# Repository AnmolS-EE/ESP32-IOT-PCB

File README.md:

# ESP32-IOT-PCB
IN Progress...Stay Tuned

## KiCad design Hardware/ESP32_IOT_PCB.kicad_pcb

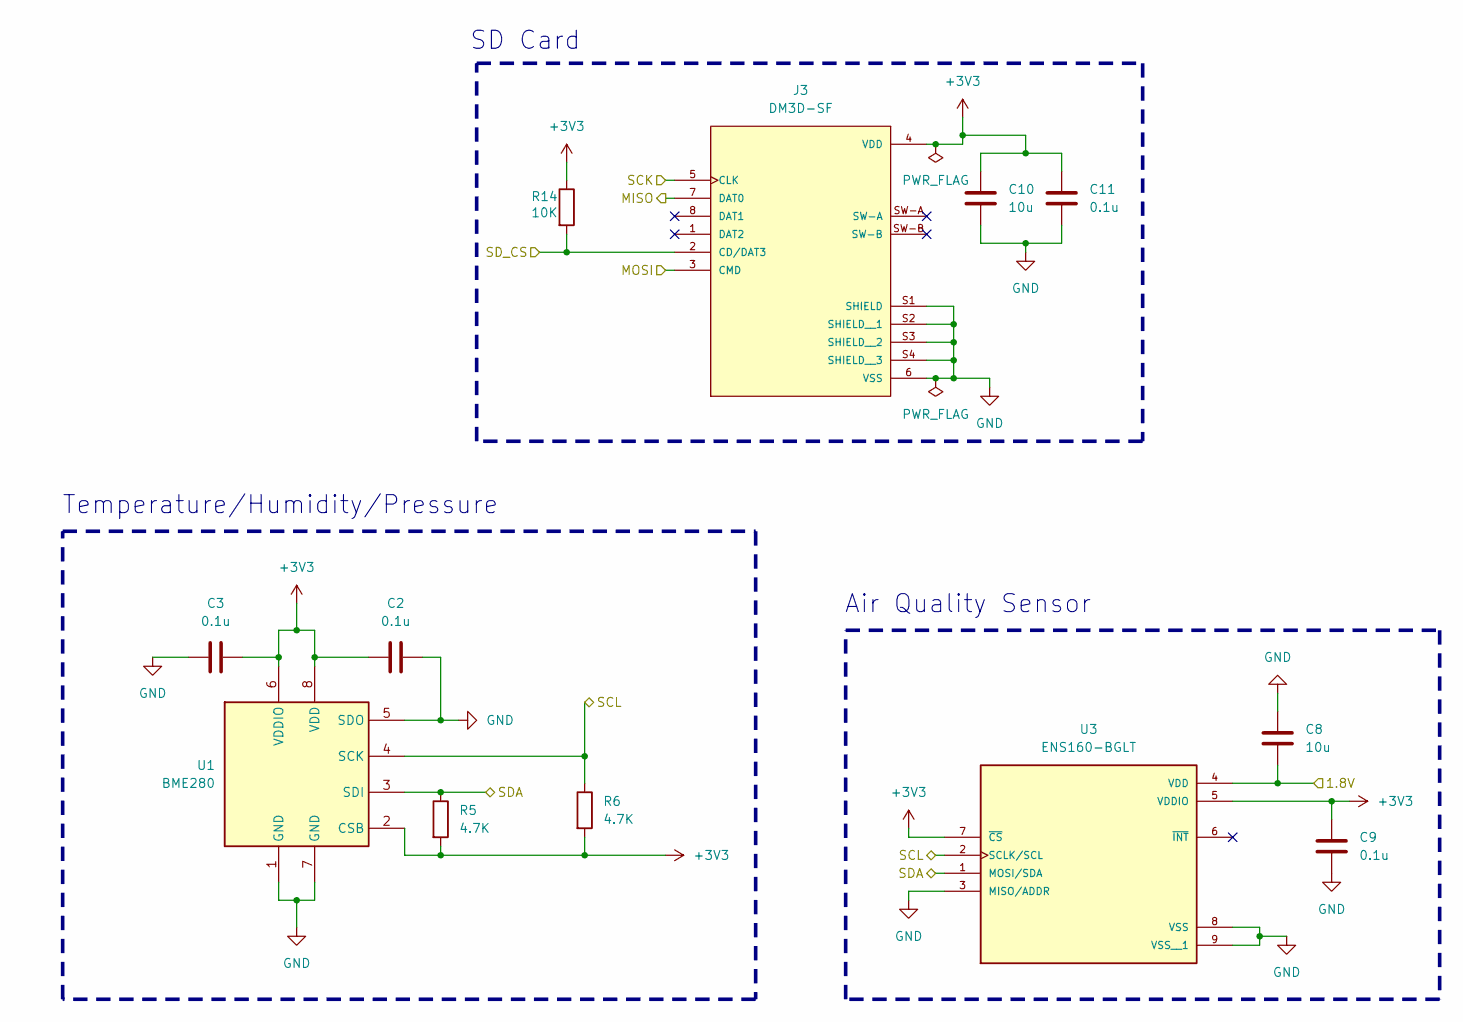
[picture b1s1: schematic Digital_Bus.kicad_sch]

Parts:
C2, C3, C9, C11: 0.1u; C_0805_2012Metric
C8, C10: 10u; C_0805_2012Metric
J3: DM3D-SF; HRS_DM3D-SF; PARTREV 2017.1
R5, R6: 4.7K; R_0805_2012Metric
R14: 10K; R_0805_2012Metric
U1: BME280; Bosch_LGA-8_2.5x2.5mm_P0.65mm_ClockwisePinNumbering
U3: ENS160-BGLT; XDCR_ENS160-BGLT; PARTREV 1.3

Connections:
+3V3: C2.1, C3.1, C9.1, C10.1, C11.1, J3.4 (VDD), R5.2, R6.2, R14.1, U1.2 (CSB), U1.6 (VDDIO), U1.8 (VDD), U3.5 (VDDIO), U3.7 (~CS); also elsewhere on the board
/Digital Bus/1.8V: C8.2, U3.4 (VDD); also elsewhere on the board
/Digital Bus/MISO: J3.7 (DAT0); also elsewhere on the board
/Digital Bus/MOSI: J3.3 (CMD); also elsewhere on the board
/Digital Bus/SCK: J3.5 (CLK); also elsewhere on the board
/Digital Bus/SCL: R6.1, U1.4 (SCK), U3.2 (SCLK/SCL); also elsewhere on the board
/Digital Bus/SDA: R5.1, U1.3 (SDI), U3.1 (MOSI/SDA); also elsewhere on the board
/Digital Bus/SD_CS: J3.2 (CD/DAT3), R14.2; also elsewhere on the board
GND: C2.2, C3.2, C8.1, C9.2, C10.2, C11.2, J3.6 (VSS), J3.S1 (SHIELD), J3.S2 (SHIELD__1), J3.S3 (SHIELD__2), J3.S4 (SHIELD__3), U1.1 (GND), U1.5 (SDO), U1.7 (GND), U3.3 (MISO/ADDR), U3.8 (VSS), U3.9 (VSS__1); also elsewhere on the board

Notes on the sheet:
SD Card
Temperature/Humidity/Pressure
Air Quality Sensor

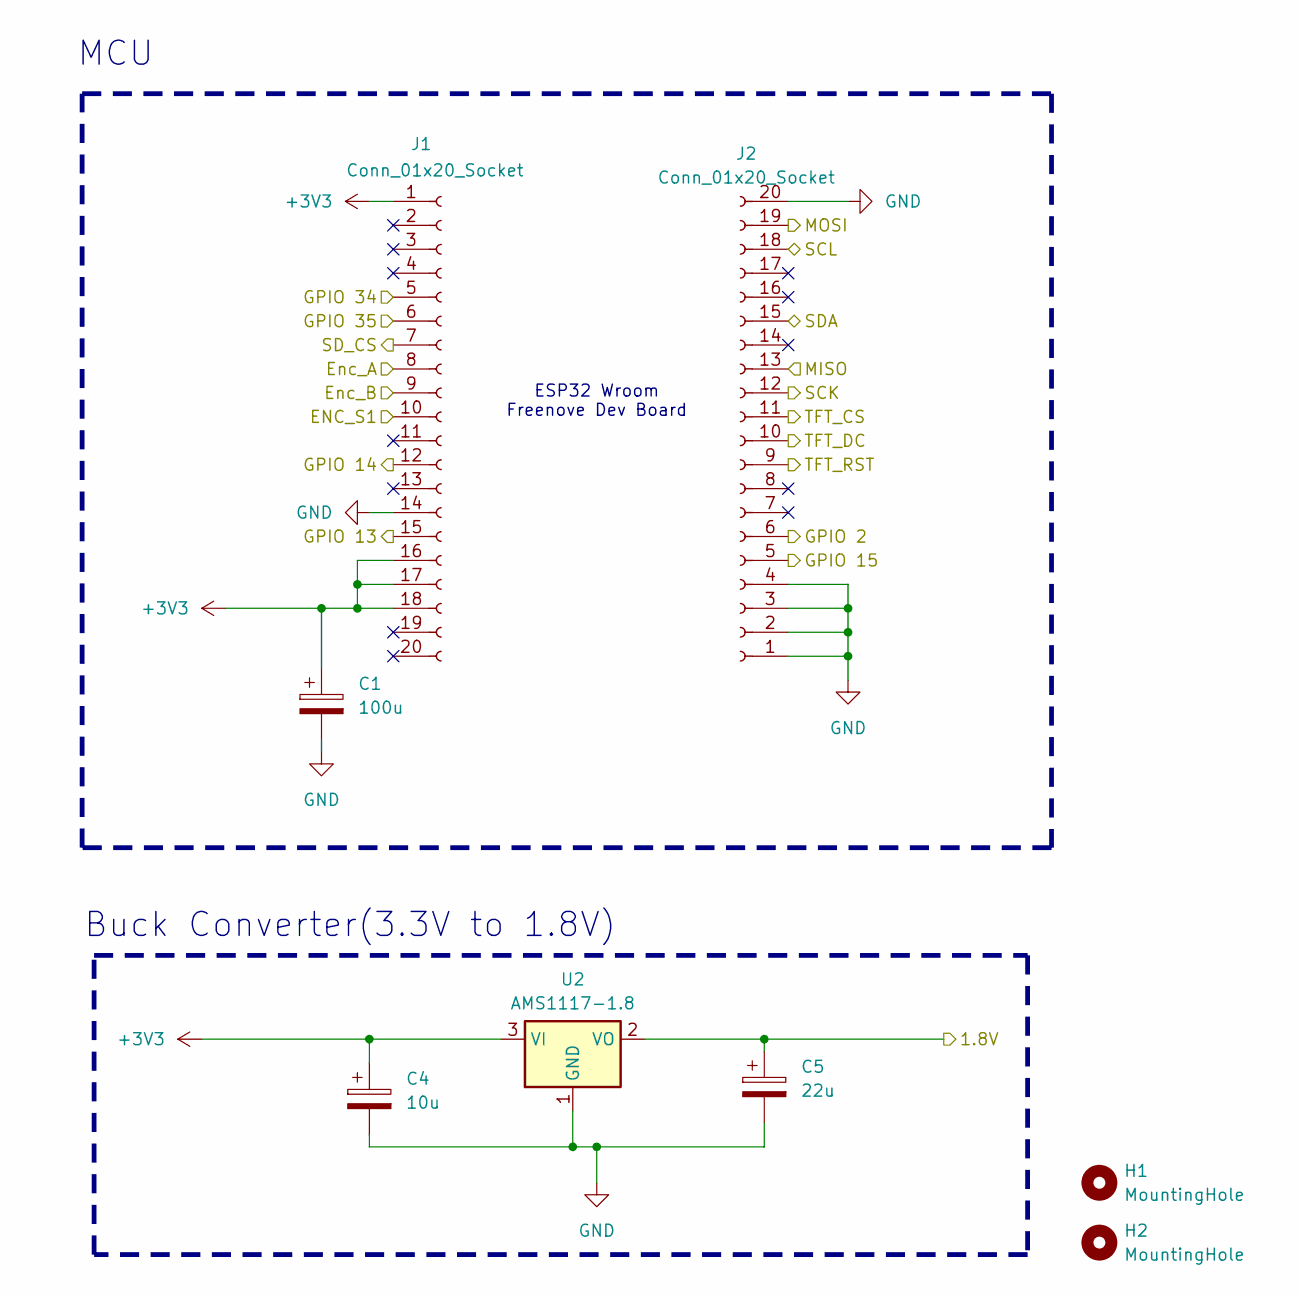
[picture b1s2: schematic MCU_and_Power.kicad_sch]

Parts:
C1: 100u; CP_Radial_D6.3mm_P2.50mm
C4: 10u; CP_Radial_D5.0mm_P2.00mm
C5: 22u; CP_Radial_D5.0mm_P2.00mm
H1, H2: MountingHole; MountingHole_3.2mm_M3
J1, J2: Conn_01x20_Socket; PinSocket_1x20_P2.54mm_Vertical
U2: AMS1117-1.8; SOT-223-3_TabPin2

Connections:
+3V3: C1.1, C4.1, J1.1, J1.16, J1.17, J1.18, U2.3 (VI); also elsewhere on the board
/Analog Audio Engine/GPIO 34: J1.5; also elsewhere on the board
/Analog Audio Engine/GPIO 35: J1.6; also elsewhere on the board
/Digital Bus/1.8V: C5.1, U2.2 (VO); also elsewhere on the board
/Digital Bus/MISO: J2.13; also elsewhere on the board
/Digital Bus/MOSI: J2.19; also elsewhere on the board
/Digital Bus/SCK: J2.12; also elsewhere on the board
/Digital Bus/SCL: J2.18; also elsewhere on the board
/Digital Bus/SDA: J2.15; also elsewhere on the board
/Digital Bus/SD_CS: J1.7; also elsewhere on the board
/MCU and Power/ENC_S1: J1.10; also elsewhere on the board
/MCU and Power/Enc_A: J1.8; also elsewhere on the board
/MCU and Power/Enc_B: J1.9; also elsewhere on the board
/MCU and Power/GPIO 2: J2.6; also elsewhere on the board
/MCU and Power/GPIO 13: J1.15; also elsewhere on the board
/MCU and Power/GPIO 14: J1.12; also elsewhere on the board
/MCU and Power/GPIO 15: J2.5; also elsewhere on the board
/MCU and Power/TFT_CS: J2.11; also elsewhere on the board
/MCU and Power/TFT_DC: J2.10; also elsewhere on the board
/MCU and Power/TFT_RST: J2.9; also elsewhere on the board
GND: C1.2, C4.2, C5.2, J1.14, J2.1, J2.2, J2.3, J2.4, J2.20, U2.1 (GND); also elsewhere on the board

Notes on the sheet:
Buck Converter(3.3V to 1.8V)
MCU
ESP32 Wroom Freenove Dev Board

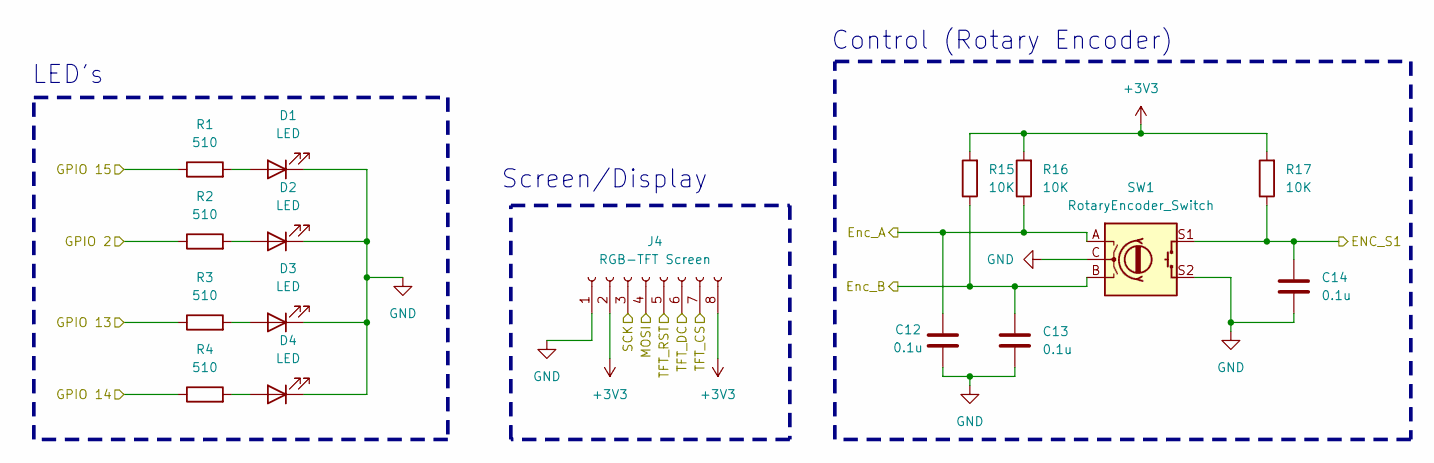
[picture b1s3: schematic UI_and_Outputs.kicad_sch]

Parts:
C12, C13, C14: 0.1u; C_0805_2012Metric
D1, D2, D3, D4: LED; LED_D3.0mm
J4: RGB-TFT Screen; 1.8_128x160_RGB-TFT
R1, R2, R3, R4: 510; R_0805_2012Metric
R15, R16, R17: 10K; R_0805_2012Metric
SW1: RotaryEncoder_Switch; RotaryEncoder_Alps_EC11E-Switch_Vertical_H20mm; LCSC C202365

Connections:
+3V3: J4.2, J4.8, R15.2, R16.2, R17.2; also elsewhere on the board
/Digital Bus/MOSI: J4.4; also elsewhere on the board
/Digital Bus/SCK: J4.3; also elsewhere on the board
/MCU and Power/ENC_S1: C14.1, R17.1, SW1.S1; also elsewhere on the board
/MCU and Power/Enc_A: C12.1, R16.1, SW1.A; also elsewhere on the board
/MCU and Power/Enc_B: C13.1, R15.1, SW1.B; also elsewhere on the board
/MCU and Power/GPIO 2: R2.1; also elsewhere on the board
/MCU and Power/GPIO 13: R3.1; also elsewhere on the board
/MCU and Power/GPIO 14: R4.1; also elsewhere on the board
/MCU and Power/GPIO 15: R1.1; also elsewhere on the board
/MCU and Power/TFT_CS: J4.7; also elsewhere on the board
/MCU and Power/TFT_DC: J4.6; also elsewhere on the board
/MCU and Power/TFT_RST: J4.5; also elsewhere on the board
GND: C12.2, C13.2, C14.2, D1.1 (K), D2.1 (K), D3.1 (K), D4.1 (K), J4.1, SW1.C, SW1.S2; also elsewhere on the board
unnamed: D1.2 (A), R1.2
unnamed: D2.2 (A), R2.2
unnamed: D3.2 (A), R3.2
unnamed: D4.2 (A), R4.2

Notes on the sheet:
Control (Rotary Encoder)
LED's
Screen/Display

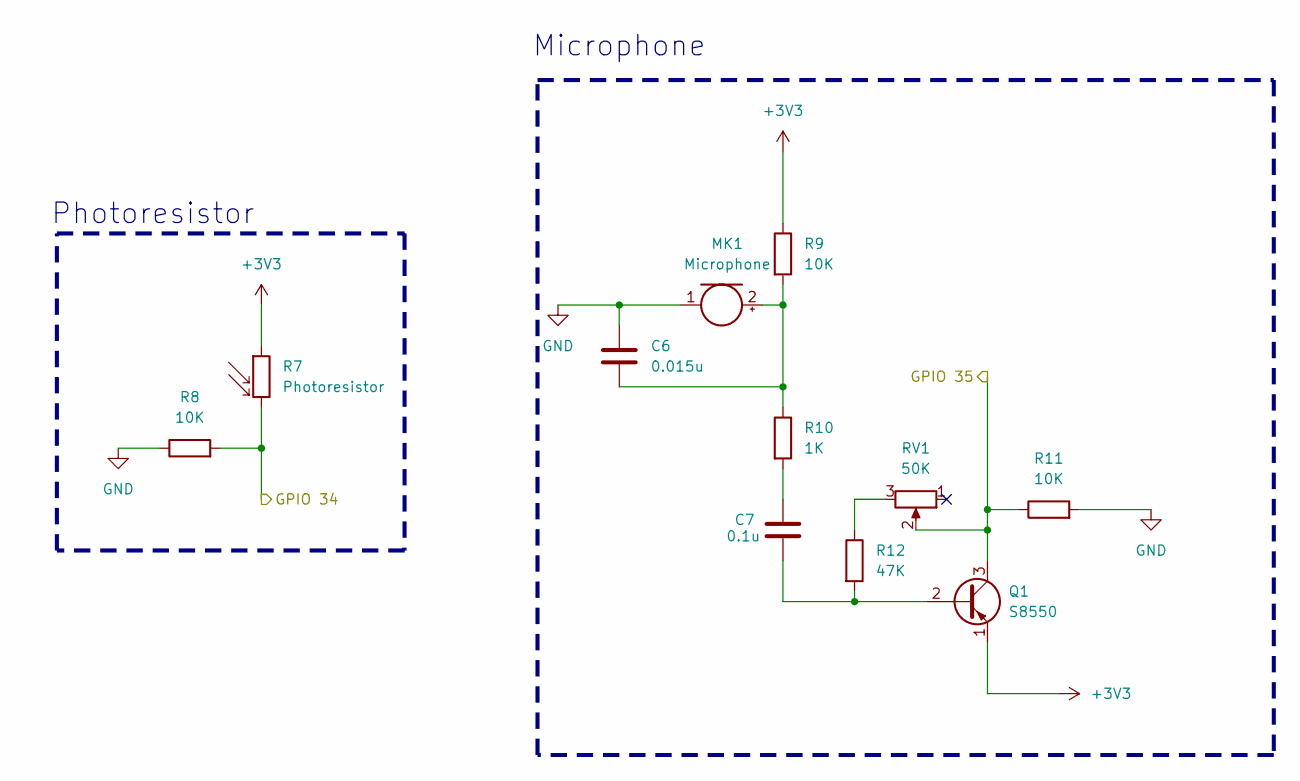
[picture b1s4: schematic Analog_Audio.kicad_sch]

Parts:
C6: 0.015u; C_Disc_D4.3mm_W1.9mm_P5.00mm
C7: 0.1u; C_0805_2012Metric
MK1: Microphone; PinHeader_1x02_P2.54mm_Vertical
Q1: S8550; TO-92_Inline
R7: Photoresistor; R_LDR_5.1x4.3mm_P3.4mm_Vertical
R8, R9, R11: 10K; R_0805_2012Metric
R10: 1K; R_0805_2012Metric
R12: 47K; R_0805_2012Metric
RV1: 50K; Potentiometer_Bourns_3314J_Vertical; LCSC C50895

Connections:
+3V3: Q1.1 (E), R7.1, R9.1; also elsewhere on the board
/Analog Audio Engine/GPIO 34: R7.2, R8.2; also elsewhere on the board
/Analog Audio Engine/GPIO 35: Q1.3 (C), R11.1, RV1.2; also elsewhere on the board
GND: C6.1, MK1.1 (-), R8.1, R11.2; also elsewhere on the board
unnamed: C7.1, R10.2
unnamed: C6.2, MK1.2 (+), R9.2, R10.1
unnamed: C7.2, Q1.2 (B), R12.2
unnamed: R12.1, RV1.3

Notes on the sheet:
Photoresistor
Microphone

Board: 2 copper layers, 47 parts (0 on the bottom side), 29 nets, no tracks yet.

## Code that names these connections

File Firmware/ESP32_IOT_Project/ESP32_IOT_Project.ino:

#include <Adafruit_GFX.h>
#include <Adafruit_ST7735.h>
#include <SPI.h>
#include <DHT.h>

// --- Pin Definitions ---
#define TFT_CS    5
#define TFT_RST   16
#define TFT_DC    17

#define DHTPIN    4
#define DHTTYPE   DHT11 
#define LDR_PIN   34
#define MIC_PIN   35

// --- Rotary Encoder Pins ---
#define ENCODER_CLK 27
#define ENCODER_DT  26
#define ENCODER_SW  25 // Reusing your old button pin for the encoder's button

// LEDs
const int numLEDs = 4;
int ledPins[numLEDs] = {15, 21, 22, 2};

// --- Objects ---
Adafruit_ST7735 tft = Adafruit_ST7735(TFT_CS, TFT_DC, TFT_RST);
DHT dht(DHTPIN, DHTTYPE);

// --- State Machine Variables ---
int currentMode = 0; 

// --- Encoder Variables ---
volatile int encoderCount = 0;       // Volatile because it changes inside the Interrupt
volatile int lastClkState = HIGH;
const int stepsPerPage = 10;         // 10 steps = half a cycle on a standard 20-step encoder

int buttonState = HIGH;             
int lastButtonState = HIGH;         
unsigned long lastDebounceTime = 0;
const unsigned long debounceDelay = 50; 

// --- Mode 0 (Weather) Variables ---
unsigned long lastWeatherUpdate = 0;
const int WEATHER_INTERVAL = 2000;
const int DARK_THRESHOLD = 1000;

// --- Mode 1 (Audio Graph) Variables ---
int xPos = 0;
const int CLAP_THRESHOLD = 400;     // Tweak this to change mic sensitivity!
unsigned long ledFlashTimer = 0;    
bool ledsFlashing = false;          

// --- Interrupt Service Routine for Encoder ---
// This runs instantly in the background whenever the dial is turned
void IRAM_ATTR updateEncoderISR() {
  int clkState = digitalRead(ENCODER_CLK);
  // Only trigger on the rising edge of the CLK signal
  if (clkState != lastClkState && clkState == HIGH) {
    if (digitalRead(ENCODER_DT) == LOW) {
      encoderCount++; // Clockwise
    } else {
      encoderCount--; // Counter-Clockwise
    }
  }
  lastClkState = clkState;
}

void setup() {
  Serial.begin(115200);

  // Initialize Encoder Pins
  pinMode(ENCODER_CLK, INPUT_PULLUP);
  pinMode(ENCODER_DT, INPUT_PULLUP);
  pinMode(ENCODER_SW, INPUT_PULLUP);

  // Attach the interrupt to the CLK pin
  attachInterrupt(digitalPinToInterrupt(ENCODER_CLK), updateEncoderISR, CHANGE);

  for (int i = 0; i < numLEDs; i++) {
    pinMode(ledPins[i], OUTPUT);
    digitalWrite(ledPins[i], LOW);
  }

  dht.begin();
  tft.initR(INITR_BLACKTAB); 
  tft.setRotation(1); 
  tft.fillScreen(ST77XX_BLACK);
  
  drawWeatherUI();
}

void loop() {
  // ---------------------------------------------------------
  // 1. PAGE NAVIGATION CHECK (Spinning or Clicking)
  // ---------------------------------------------------------
  bool changePageTriggered = false;

  // Check 1: Did we spin a half cycle (10 steps in either direction)?
  if (abs(encoderCount) >= stepsPerPage) {
    encoderCount = 0; // Reset counter for the next half-cycle
    changePageTriggered = true;
  }

  // Check 2: Did we click the encoder button down?
  int reading = digitalRead(ENCODER_SW);
  if (reading != lastButtonState) {
    lastDebounceTime = millis();
  }
  if ((millis() - lastDebounceTime) > debounceDelay) {
    if (reading != buttonState) {
      buttonState = reading;
      if (buttonState == LOW) {
        changePageTriggered = true;
      }
    }
  }
  lastButtonState = reading;

  // If either action happened, swap the page
  if (changePageTriggered) {
    currentMode = (currentMode == 0) ? 1 : 0;
    tft.fillScreen(ST77XX_BLACK);
    
    if (currentMode == 0) {
      drawWeatherUI();
      lastWeatherUpdate = 0; 
    } else if (currentMode == 1) {
      for (int i = 0; i < numLEDs; i++) digitalWrite(ledPins[i], LOW);
      xPos = 0; 
      ledsFlashing = false; 
    }
  }

  // ---------------------------------------------------------
  // 2. RUN THE ACTIVE MODE
  // ---------------------------------------------------------
  if (currentMode == 0) {
    runWeatherMode();
  } else if (currentMode == 1) {
    runAudioMode();
  }
}

// --- Helper Functions ---

void drawWeatherUI() {
  tft.setTextColor(ST77XX_CYAN);
  tft.setTextSize(2);
  tft.setCursor(10, 10);
  tft.print("Sensor Dash");
  
  tft.setTextColor(ST77XX_WHITE);
  tft.setTextSize(1);
  tft.setCursor(10, 50);
  tft.print("Temp:");
  tft.setCursor(10, 80);
  tft.print("Humidity:");
  tft.setCursor(10, 110);
  tft.print("Light Lvl:");
}

void runWeatherMode() {
  int lightLevel = analogRead(LDR_PIN);
  bool isDark = (lightLevel < DARK_THRESHOLD);
  for (int i = 0; i < numLEDs; i++) {
    digitalWrite(ledPins[i], isDark ? HIGH : LOW);
  }

  if (millis() - lastWeatherUpdate > WEATHER_INTERVAL) {
    lastWeatherUpdate = millis(); 

    float h = dht.readHumidity();
    float t = dht.readTemperature(); 

    tft.fillRect(70, 50, 80, 15, ST77XX_BLACK);
    tft.setCursor(70, 50);
    if (isnan(t)) tft.print("Err"); else { tft.print(t); tft.print(" C"); }

    tft.fillRect(70, 80, 80, 15, ST77XX_BLACK);
    tft.setCursor(70, 80);
    if (isnan(h)) tft.print("Err"); else { tft.print(h); tft.print(" %"); }

    tft.fillRect(80, 110, 50, 15, ST77XX_BLACK);
    tft.setCursor(80, 110);
    tft.print(lightLevel);
  }
}

void runAudioMode() {
  int maxVal = 0;
  int minVal = 4095; 

  for(int i = 0; i < 20; i++) {
    int val = analogRead(MIC_PIN);
    if (val > maxVal) maxVal = val;
    if (val < minVal) minVal = val;
  }

  int noiseLevel = maxVal - minVal;

  int yPos = map(maxVal, 0, 4095, 120, 10);
  tft.drawPixel(xPos, yPos, ST77XX_GREEN);
  xPos++;

  if (xPos >= 160) { 
    xPos = 0;
    tft.fillScreen(ST77XX_BLACK); 
  }
  
  if (noiseLevel > CLAP_THRESHOLD) {
    for (int i = 0; i < numLEDs; i++) digitalWrite(ledPins[i], HIGH);
    ledsFlashing = true;
    ledFlashTimer = millis(); 
  }

  if (ledsFlashing && (millis() - ledFlashTimer > 100)) {
    for (int i = 0; i < numLEDs; i++) digitalWrite(ledPins[i], LOW);
    ledsFlashing = false;
  }
  
  delay(5); 
}

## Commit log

2026-05-23 Added initial hardware and firmware
2026-05-25 Major Updates to Schematic
2026-05-25 Add progress note to README
2026-05-26 Schematic V0.9 is complete
